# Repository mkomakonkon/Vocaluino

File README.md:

# Vocaluino
MIDI device for playing drum, vocal, PSG, etc with Arduino.

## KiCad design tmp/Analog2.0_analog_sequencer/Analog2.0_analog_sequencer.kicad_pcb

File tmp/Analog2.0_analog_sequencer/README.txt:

本データはAnalog2.0のアナログシーケンサーを改良したものです。
ライセンスはAnalog2.0に従ってください。

Analog2.0のホームページ
https://gaje.jp/analog20/

デモ動画
https://youtu.be/-u9PDCDGB98

CADデータはKiCAD用です。
配置配線案は秋月の下記ユニバーサル基板用の物です。
【P-02188】　両面ガラス・ユニバーサル基板　大タイプ２．５４ｍｍピッチ　（２１０×１５５ｍｍ）
フォンジャックは、お手製の変換基板を使ってて参考にならないと思うので修正してください。

変更内容-----------------------------------------------
オリジナルはシーケンサーが動作していない時も
Gate outが出続けるため、シーケンサー停止時に
Gate outを止めるための変更をした。

・4051の出力をダイオードでORして
Gate out制御用トランジスタのベースに入力することで、
4051が動作しているときのみコレクタを流れるGate out信号をON。
それ以外はGate out信号をOFF。
出力を低インピーダンスにするためエミッタフォロワとする。

・スイッチOFF時も上記回路が動作するように
スイッチの位置を変更。

・念のため回路図に記載のないパスコンを追加。

制約事項-----------------------------------------------
変更を最小限にするため以下の制約あり。
・Gate outは非同期で自走しているため、
　スタートのタイミングによっては1発目の音が出ない。
・Gate out→4051の遅延を吸収していないため
　Gate out OFF直前に不要なパルスが出る。
・Gate out信号は電源よりレベルが低いため
　5V電源を使用する場合は出力にバッファを設けた方が良い。
　12V電源であれば実害はないが、5V入力の機器にはGate outを接続しないこと。
　(Analog2.0は問題ないはず）)

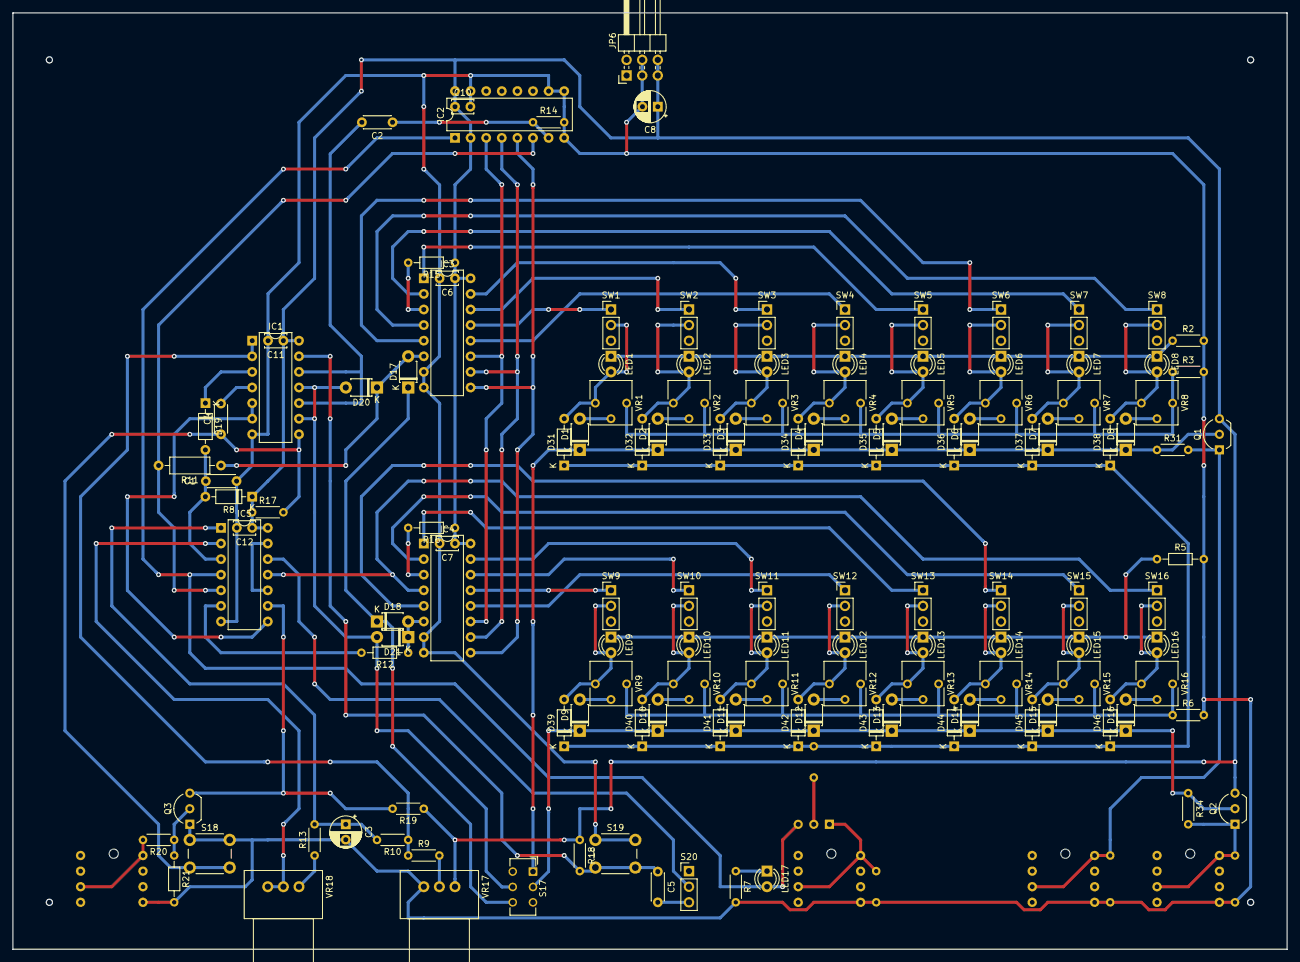
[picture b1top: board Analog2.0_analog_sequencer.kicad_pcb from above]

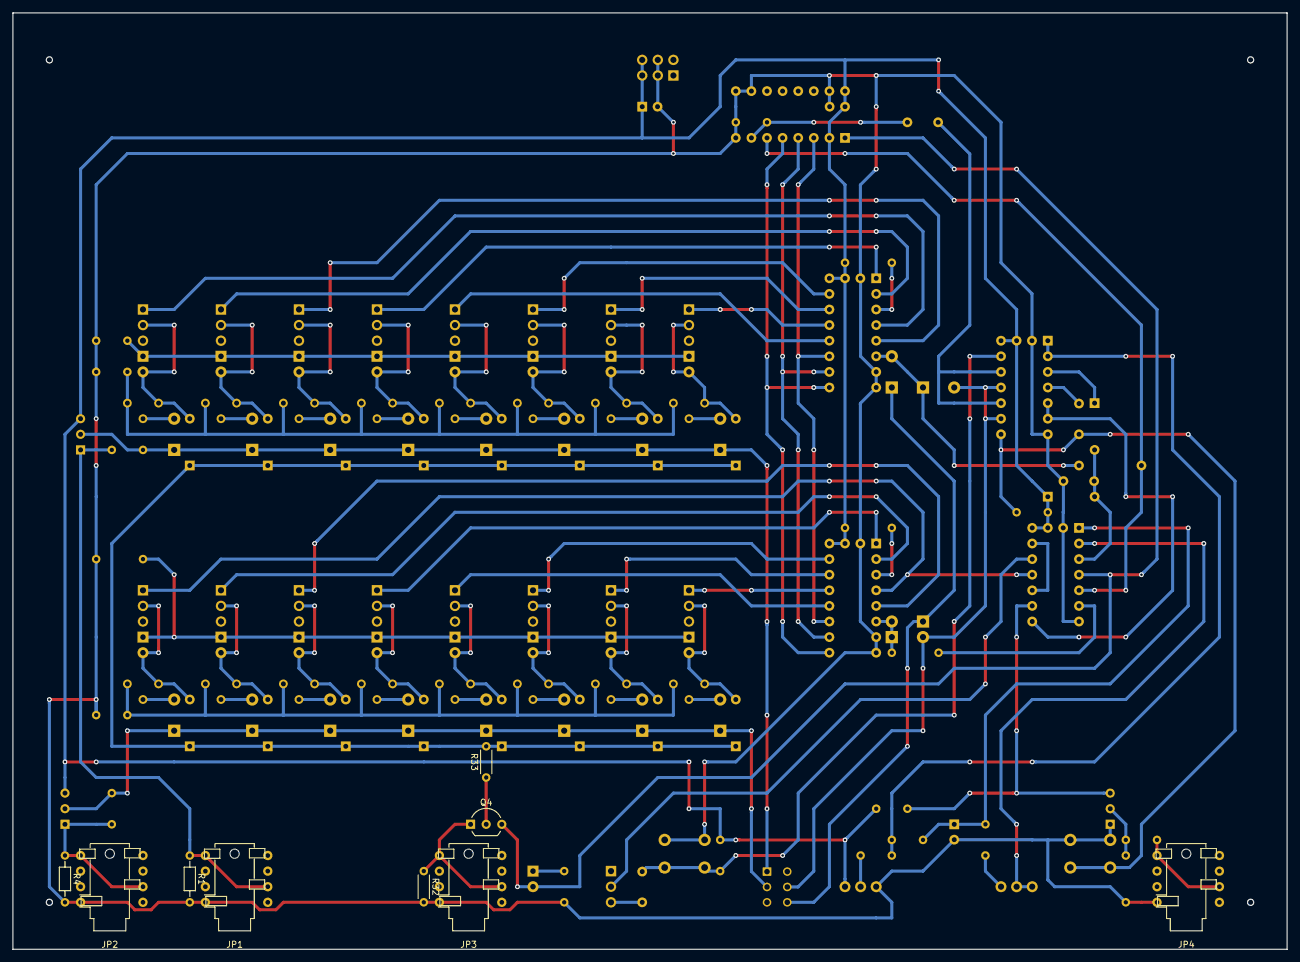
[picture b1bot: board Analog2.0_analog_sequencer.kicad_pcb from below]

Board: 2 copper layers, 207.5 x 152.5 mm, 142 parts (9 on the bottom side), 93 nets.

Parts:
C1: 0.022u; C_Disc_D4.3mm_W1.9mm_P5.00mm
C2, C4, C5: 0.1u; C_Disc_D4.3mm_W1.9mm_P5.00mm
C3: 22u; CP_Radial_D5.0mm_P2.50mm
C6, C7, C10, C11, C12: 0.1u; C_Disc_D3.4mm_W2.1mm_P2.50mm
C8: 100u; CP_Radial_D5.0mm_P2.50mm
D1, D2, D3, D4, D5, D6, D7, D8, D9, D10, D11, D12, D13, D14, D15, D16: D; D_T-1_P5.08mm_Horizontal
D17, D18, D20, D21: 1N4148; D_T-1_P5.08mm_Horizontal
D19: 1N4148; D_DO-35_SOD27_P7.62mm_Horizontal
D31, D32, D33, D34, D35, D36, D37, D38, D39, D40, D41, D42, D43, D44, D45, D46: D; D_DO-35_SOD27_P7.62mm_Horizontal
IC1: 4011; DIP-14_W7.62mm
IC2: 4520; DIP-16_W7.62mm
IC3, IC4: 4051; DIP-16_W7.62mm
IC5: 4584; DIP-14_W7.62mm
JP1: CV_OUT1; Jack_3.5mm_HSJ1828
JP2: CV_OUT2; Jack_3.5mm_HSJ1828
JP3: Gate_Out; Jack_3.5mm_HSJ1828
JP4: Gate_In; Jack_3.5mm_HSJ1828
JP6: Conn_02x03_Counter_Clockwise; PinHeader_2x03_P2.54mm_Horizontal
LED1, LED2, LED3, LED4, LED5, LED6, LED7, LED8, LED9, LED10, LED11, LED12, LED13, LED14, LED15, LED16, LED17: LED; LED_D3.0mm
Q1, Q2, Q3, Q4: 2N3904; TO-92_Inline_Wide
R1, R4: 2.2K; R_Axial_DIN0204_L3.6mm_D1.6mm_P7.62mm_Horizontal
R2: 820; R_Axial_DIN0204_L3.6mm_D1.6mm_P5.08mm_Horizontal
R3, R6: 3.3K; R_Axial_DIN0204_L3.6mm_D1.6mm_P5.08mm_Horizontal
R5: 820; R_Axial_DIN0204_L3.6mm_D1.6mm_P7.62mm_Horizontal
R7: 2.2K; R_Axial_DIN0204_L3.6mm_D1.6mm_P5.08mm_Horizontal
R8: 10K; D_DO-35_SOD27_P7.62mm_Horizontal
R9: 4.7M; R_Axial_DIN0204_L3.6mm_D1.6mm_P5.08mm_Horizontal
R10, R31, R34: 1M; R_Axial_DIN0204_L3.6mm_D1.6mm_P5.08mm_Horizontal
R11: 100K; R_Axial_DIN0207_L6.3mm_D2.5mm_P10.16mm_Horizontal
R12, R21: 100K; R_Axial_DIN0204_L3.6mm_D1.6mm_P7.62mm_Horizontal
R13, R14: 4.7K; R_Axial_DIN0204_L3.6mm_D1.6mm_P5.08mm_Horizontal
R15, R16: 220; R_Axial_DIN0204_L3.6mm_D1.6mm_P7.62mm_Horizontal
R17, R18: 10K; R_Axial_DIN0204_L3.6mm_D1.6mm_P5.08mm_Horizontal
R19: 22K; R_Axial_DIN0204_L3.6mm_D1.6mm_P5.08mm_Horizontal
R20, R32, R33: 47K; R_Axial_DIN0204_L3.6mm_D1.6mm_P5.08mm_Horizontal
S17: Para/Seri; SW_CuK_JS202011CQN_DPDT_Straight
S18: SW_Start; SW_PUSH_6mm_H5mm
S19: SW_Stop; SW_PUSH_6mm_H5mm
S20: SW_Push_SPDT; PinHeader_1x03_P2.54mm_Vertical
SW1, SW2, SW3, SW4, SW5, SW6, SW7, SW8, SW9, SW10, SW11, SW12, SW13, SW14, SW15, SW16: SW_SPDT; PinHeader_1x03_P2.54mm_Vertical
VR1, VR2, VR3, VR4, VR5, VR6, VR7, VR8, VR9, VR10, VR11, VR12, VR13, VR14, VR15, VR16: B50K; Potentiometer_Vishay_T73YP_Vertical
VR17, VR18: B50K; Potentiometer_Vishay_248GJ-249GJ_Single_Horizontal

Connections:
+12V: C6.1, C7.1, C8.1, C10.1, C11.1, C12.1, IC1.14, IC2.2, IC2.16, IC3.16, IC4.16, IC5.14, JP6.5, JP6.6, Q1.3, Q2.3, R8.1, R15.1, R16.1, R17.1, R18.1, R19.1, VR17.3
CV_OUT1: JP1.R, JP1.T, Q1.1, R1.1, R31.2
CV_OUT2: JP2.R, JP2.T, Q2.1, R4.1, R34.2
GND: C1.2, C3.2, C6.2, C7.2, C8.2, C10.2, C11.2, C12.2, IC1.7, IC2.8, IC2.9, IC2.10, IC2.15, IC3.7, IC3.8, IC4.7, IC4.8, IC5.7, JP1.S, JP2.S, JP3.S, JP4.S, JP6.3, JP6.4, Q3.1, R1.2, R2.2, R3.2, R4.2, R5.2, R6.2, R7.2, R14.2, R21.2, R32.2, S18.1, S19.1, VR17.1
Gate_In: JP4.R, JP4.T, R20.2
Gate_Out: JP3.R, JP3.T, Q4.1, R32.1
unnamed: C1.1, D19.2, IC5.3, R8.2
unnamed: C2.1, IC2.7, R14.1
unnamed: C2.2, IC1.10, IC1.12
unnamed: C3.1, IC5.1, R10.2, R13.2
unnamed: C4.1, IC1.8, R17.2, S18.2
unnamed: C4.2, IC1.4
unnamed: C5.1, IC1.13, R18.2, S19.2
unnamed: C5.2, S20.3
unnamed: D1.1, D2.1, D3.1, D4.1, D5.1, D6.1, D7.1, D8.1, Q1.2, R31.1, S17.1
unnamed: D1.2, VR1.2
unnamed: D2.2, VR2.2
unnamed: D3.2, VR3.2
unnamed: D4.2, VR4.2
unnamed: D5.2, VR5.2
unnamed: D6.2, VR6.2
unnamed: D7.2, VR7.2
unnamed: D8.2, VR8.2
unnamed: D9.2, VR9.2
unnamed: D9.1, D10.1, D11.1, D12.1, D13.1, D14.1, D15.1, D16.1, Q2.2, R34.1, S17.2
unnamed: D10.2, VR10.2
unnamed: D11.2, VR11.2
unnamed: D12.2, VR12.2
unnamed: D13.2, VR13.2
unnamed: D14.2, VR14.2
unnamed: D15.2, VR15.2
unnamed: D16.2, VR16.2
unnamed: D17.1, D18.1, S17.6
unnamed: D17.2, D20.1, IC3.6, R11.1
unnamed: D18.2, D21.1, IC4.6, R12.1
unnamed: D19.1, IC1.3
unnamed: D20.2, D21.2, IC1.9, IC1.11, S17.5
unnamed: D31.1, D32.1, D33.1, D34.1, D35.1, D36.1, D37.1, D38.1, D39.1, D40.1, D41.1, D42.1, D43.1, D44.1, D45.1, D46.1, R33.2
unnamed: D31.2, LED1.2, SW1.2, VR1.1
unnamed: D32.2, LED2.2, SW2.2, VR2.1
unnamed: D33.2, LED3.2, SW3.2, VR3.1
unnamed: D34.2, LED4.2, SW4.2, VR4.1
unnamed: D35.2, LED5.2, SW5.2, VR5.1
unnamed: D36.2, LED6.2, SW6.2, VR6.1
unnamed: D37.2, LED7.2, SW7.2, VR7.1
unnamed: D38.2, LED8.2, SW8.2, VR8.1
unnamed: D39.2, LED9.2, SW9.2, VR9.1
unnamed: D40.2, LED10.2, SW10.2, VR10.1
unnamed: D41.2, LED11.2, SW11.2, VR11.1
unnamed: D42.2, LED12.2, SW12.2, VR12.1
unnamed: D43.2, LED13.2, SW13.2, VR13.1
unnamed: D44.2, LED14.2, SW14.2, VR14.1
unnamed: D45.2, LED15.2, SW15.2, VR15.1
unnamed: D46.2, LED16.2, SW16.2, VR16.1
unnamed: IC1.1, IC1.2, R9.1, R10.1
unnamed: IC1.5, IC1.6, IC5.8
unnamed: IC2.1, IC5.4, LED17.2, Q4.3
unnamed: IC2.3, IC3.11, IC4.11
unnamed: IC2.4, IC3.10, IC4.10
unnamed: IC2.5, IC3.9, IC4.9
unnamed: IC2.6, IC5.5, R11.2
unnamed: IC3.1, SW5.1
unnamed: IC3.2, SW7.1
unnamed: IC3.3, R15.2
unnamed: IC3.4, SW8.1
unnamed: IC3.5, SW6.1
unnamed: IC3.12, SW4.1
unnamed: IC3.13, SW1.1
unnamed: IC3.14, SW2.1
unnamed: IC3.15, SW3.1
unnamed: IC4.1, SW13.1
unnamed: IC4.2, SW15.1
unnamed: IC4.3, R16.2
unnamed: IC4.4, IC5.11, SW16.1
unnamed: IC4.5, SW14.1
unnamed: IC4.12, SW12.1
unnamed: IC4.13, SW9.1
unnamed: IC4.14, SW10.1
unnamed: IC4.15, SW11.1
unnamed: IC5.2, VR18.1, VR18.2
unnamed: IC5.6, R12.2
unnamed: IC5.9, Q3.3, R19.2
unnamed: IC5.10, IC5.13
unnamed: IC5.12, S20.2
unnamed: LED1.1, LED2.1, LED3.1, LED4.1, LED5.1, LED6.1, LED7.1, LED8.1, R2.1
unnamed: LED9.1, LED10.1, LED11.1, LED12.1, LED13.1, LED14.1, LED15.1, LED16.1, R5.1
unnamed: LED17.1, R7.1
unnamed: Q3.2, R20.1, R21.1
unnamed: Q4.2, R33.1
unnamed: R3.1, VR1.3, VR2.3, VR3.3, VR4.3, VR5.3, VR6.3, VR7.3, VR8.3
unnamed: R6.1, VR9.3, VR10.3, VR11.3, VR12.3, VR13.3, VR14.3, VR15.3, VR16.3
unnamed: R9.2, VR17.2
unnamed: R13.1, VR18.3

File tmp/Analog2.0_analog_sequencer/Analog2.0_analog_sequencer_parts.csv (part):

Reference, Value, Footprint, Datasheet
"R15","220","Resistor_THT:R_Axial_DIN0204_L3.6mm_D1.6mm_P5.08mm_Horizontal","~"
"IC3","4051","Package_DIP:DIP-16_W7.62mm","http://www.intersil.com/content/dam/Intersil/documents/cd40/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"
"D1","D","Diode_THT:D_T-1_P5.08mm_Horizontal","~"
"SW1","SW_Push_SPDT","Connector_PinHeader_2.54mm:PinHeader_1x03_P2.54mm_Vertical",""
"Q1","2N3904","Package_TO_SOT_THT:TO-92_Inline_Wide","https://www.fairchildsemi.com/datasheets/2N/2N3904.pdf"
"R31","100K","Resistor_THT:R_Axial_DIN0204_L3.6mm_D1.6mm_P5.08mm_Horizontal","~"
"R1","2.2K","Resistor_THT:R_Axial_DIN0204_L3.6mm_D1.6mm_P5.08mm_Horizontal","~"
"LED1","LED","LED_THT:LED_D3.0mm","~"
"LED2","LED","LED_THT:LED_D3.0mm","~"
"LED3","LED","LED_THT:LED_D3.0mm","~"
"LED4","LED","LED_THT:LED_D3.0mm","~"
"LED5","LED","LED_THT:LED_D3.0mm","~"
"LED6","LED","LED_THT:LED_D3.0mm","~"
"LED7","LED","LED_THT:LED_D3.0mm","~"
"LED8","LED","LED_THT:LED_D3.0mm","~"
"D2","D","Diode_THT:D_T-1_P5.08mm_Horizontal","~"
"D3","D","Diode_THT:D_T-1_P5.08mm_Horizontal","~"
"D4","D","Diode_THT:D_T-1_P5.08mm_Horizontal","~"
"D5","D","Diode_THT:D_T-1_P5.08mm_Horizontal","~"
"D6","D","Diode_THT:D_T-1_P5.08mm_Horizontal","~"
"D7","D","Diode_THT:D_T-1_P5.08mm_Horizontal","~"
"D8","D","Diode_THT:D_T-1_P5.08mm_Horizontal","~"
"SW2","SW_Push_SPDT","Connector_PinHeader_2.54mm:PinHeader_1x03_P2.54mm_Vertical",""
"SW3","SW_Push_SPDT","Connector_PinHeader_2.54mm:PinHeader_1x03_P2.54mm_Vertical",""
"SW4","SW_Push_SPDT","Connector_PinHeader_2.54mm:PinHeader_1x03_P2.54mm_Vertical",""
"SW5","SW_Push_SPDT","Connector_PinHeader_2.54mm:PinHeader_1x03_P2.54mm_Vertical",""
"SW6","SW_Push_SPDT","Connector_PinHeader_2.54mm:PinHeader_1x03_P2.54mm_Vertical",""
"SW7","SW_Push_SPDT","Connector_PinHeader_2.54mm:PinHeader_1x03_P2.54mm_Vertical",""
"SW8","SW_Push_SPDT","Connector_PinHeader_2.54mm:PinHeader_1x03_P2.54mm_Vertical",""
"VR1","B50K","Potentiometer_THT:Potentiometer_Vishay_T73YP_Vertical","~"
"R2","820","Resistor_THT:R_Axial_DIN0204_L3.6mm_D1.6mm_P5.08mm_Horizontal","~"
"R16","220","Resistor_THT:R_Axial_DIN0204_L3.6mm_D1.6mm_P5.08mm_Horizontal","~"
"IC4","4051","Package_DIP:DIP-16_W7.62mm","http://www.intersil.com/content/dam/Intersil/documents/cd40/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"
"VR2","B50K","Potentiometer_THT:Potentiometer_Vishay_T73YP_Vertical","~"
"VR3","B50K","Potentiometer_THT:Potentiometer_Vishay_T73YP_Vertical","~"
"VR4","B50K","Potentiometer_THT:Potentiometer_Vishay_T73YP_Vertical","~"
"VR5","B50K","Potentiometer_THT:Potentiometer_Vishay_T73YP_Vertical","~"
"VR6","B50K","Potentiometer_THT:Potentiometer_Vishay_T73YP_Vertical","~"
"VR7","B50K","Potentiometer_THT:Potentiometer_Vishay_T73YP_Vertical","~"
"VR8","B50K","Potentiometer_THT:Potentiometer_Vishay_T73YP_Vertical","~"
"R3","3.3K","Resistor_THT:R_Axial_DIN0204_L3.6mm_D1.6mm_P5.08mm_Horizontal","~"
"D9","D","Diode_THT:D_T-1_P5.08mm_Horizontal","~"
"SW9","SW_Push_SPDT","Connector_PinHeader_2.54mm:PinHeader_1x03_P2.54mm_Vertical",""
"Q2","2N3904","Package_TO_SOT_THT:TO-92_Inline_Wide","https://www.fairchildsemi.com/datasheets/2N/2N3904.pdf"
"R34","100K","Resistor_THT:R_Axial_DIN0204_L3.6mm_D1.6mm_P5.08mm_Horizontal","~"
"R4","2.2K","Resistor_THT:R_Axial_DIN0204_L3.6mm_D1.6mm_P5.08mm_Horizontal","~"
"LED9","LED","LED_THT:LED_D3.0mm","~"
"LED10","LED","LED_THT:LED_D3.0mm","~"
"LED11","LED","LED_THT:LED_D3.0mm","~"
"LED12","LED","LED_THT:LED_D3.0mm","~"
"LED13","LED","LED_THT:LED_D3.0mm","~"
"LED14","LED","LED_THT:LED_D3.0mm","~"
"LED15","LED","LED_THT:LED_D3.0mm","~"
"LED16","LED","LED_THT:LED_D3.0mm","~"
"D10","D","Diode_THT:D_T-1_P5.08mm_Horizontal","~"
"D11","D","Diode_THT:D_T-1_P5.08mm_Horizontal","~"
"D12","D","Diode_THT:D_T-1_P5.08mm_Horizontal","~"
"D13","D","Diode_THT:D_T-1_P5.08mm_Horizontal","~"
"D14","D","Diode_THT:D_T-1_P5.08mm_Horizontal","~"
"D15","D","Diode_THT:D_T-1_P5.08mm_Horizontal","~"
"D16","D","Diode_THT:D_T-1_P5.08mm_Horizontal","~"
"SW10","SW_Push_SPDT","Connector_PinHeader_2.54mm:PinHeader_1x03_P2.54mm_Vertical",""
"SW11","SW_Push_SPDT","Connector_PinHeader_2.54mm:PinHeader_1x03_P2.54mm_Vertical",""
"SW12","SW_Push_SPDT","Connector_PinHeader_2.54mm:PinHeader_1x03_P2.54mm_Vertical",""
"SW13","SW_Push_SPDT","Connector_PinHeader_2.54mm:PinHeader_1x03_P2.54mm_Vertical",""
"SW14","SW_Push_SPDT","Connector_PinHeader_2.54mm:PinHeader_1x03_P2.54mm_Vertical",""
"SW15","SW_Push_SPDT","Connector_PinHeader_2.54mm:PinHeader_1x03_P2.54mm_Vertical",""
"SW16","SW_Push_SPDT","Connector_PinHeader_2.54mm:PinHeader_1x03_P2.54mm_Vertical",""
"VR9","B50K","Potentiometer_THT:Potentiometer_Vishay_T73YP_Vertical","~"
"R5","820","Resistor_THT:R_Axial_DIN0204_L3.6mm_D1.6mm_P5.08mm_Horizontal","~"
"VR10","B50K","Potentiometer_THT:Potentiometer_Vishay_T73YP_Vertical","~"
"VR11","B50K","Potentiometer_THT:Potentiometer_Vishay_T73YP_Vertical","~"
"VR12","B50K","Potentiometer_THT:Potentiometer_Vishay_T73YP_Vertical","~"
"VR13","B50K","Potentiometer_THT:Potentiometer_Vishay_T73YP_Vertical","~"
"VR14","B50K","Potentiometer_THT:Potentiometer_Vishay_T73YP_Vertical","~"
"VR15","B50K","Potentiometer_THT:Potentiometer_Vishay_T73YP_Vertical","~"
"VR16","B50K","Potentiometer_THT:Potentiometer_Vishay_T73YP_Vertical","~"
"R6","3.3K","Resistor_THT:R_Axial_DIN0204_L3.6mm_D1.6mm_P5.08mm_Horizontal","~"
"S17","Para/Seri","Button_Switch_THT:SW_CuK_JS202011CQN_DPDT_Straight",""
"IC2","4520","Package_DIP:DIP-16_W7.62mm","http://www.intersil.com/content/dam/Intersil/documents/cd45/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"
"D18","1N4148","Diode_THT:D_T-1_P5.08mm_Horizontal","~"
"D17","1N4148","Diode_THT:D_T-1_P5.08mm_Horizontal","~"
"R11","100K","Resistor_THT:R_Axial_DIN0204_L3.6mm_D1.6mm_P5.08mm_Horizontal","~"
"IC5","4584","Package_DIP:DIP-14_W7.62mm",""
"R12","100K","Resistor_THT:R_Axial_DIN0204_L3.6mm_D1.6mm_P5.08mm_Horizontal","~"
"D21","1N4148","Diode_THT:D_T-1_P5.08mm_Horizontal","~"
"D20","1N4148","Diode_THT:D_T-1_P5.08mm_Horizontal","~"
"IC1","4011","Package_DIP:DIP-14_W7.62mm","http://www.intersil.com/content/dam/Intersil/documents/cd40/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"
"C7","0.1u","Capacitor_THT:C_Disc_D3.4mm_W2.1mm_P2.50mm","~"
"C6","0.1u","Capacitor_THT:C_Disc_D3.4mm_W2.1mm_P2.50mm","~"
"C2","0.1u","Capacitor_THT:C_Disc_D4.3mm_W1.9mm_P5.00mm","~"
"R14","4.7K","Resistor_THT:R_Axial_DIN0204_L3.6mm_D1.6mm_P5.08mm_Horizontal","~"
"C1","0.022u","Capacitor_THT:C_Disc_D4.3mm_W1.9mm_P5.00mm","~"
"R8","10K","Resistor_THT:R_Axial_DIN0204_L3.6mm_D1.6mm_P5.08mm_Horizontal","~"
"R7","2.2K","Resistor_THT:R_Axial_DIN0204_L3.6mm_D1.6mm_P5.08mm_Horizontal","~"
"LED17","LED","LED_THT:LED_D3.0mm","~"
"D19","1N4148","Diode_THT:D_T-1_P5.08mm_Horizontal","~"
"VR17","B50K","Potentiometer_THT:Potentiometer_Vishay_248GJ-249GJ_Single_Horizontal","~"
"VR18","B50K","Potentiometer_THT:Potentiometer_Vishay_248GJ-249GJ_Single_Horizontal","~"
"R9","4.7M","Resistor_THT:R_Axial_DIN0204_L3.6mm_D1.6mm_P5.08mm_Horizontal","~"
"R10","1M","Resistor_THT:R_Axial_DIN0204_L3.6mm_D1.6mm_P5.08mm_Horizontal","~"
"R13","4.7K","Resistor_THT:R_Axial_DIN0204_L3.6mm_D1.6mm_P5.08mm_Horizontal","~"
"C3","22u","Capacitor_THT:CP_Radial_D5.0mm_P2.50mm","~"
"R18","10K","Resistor_THT:R_Axial_DIN0204_L3.6mm_D1.6mm_P5.08mm_Horizontal","~"
"S19","SW_Start","Button_Switch_THT:SW_PUSH_6mm_H5mm",""
"C5","0.1u","Capacitor_THT:C_Disc_D4.3mm_W1.9mm_P5.00mm","~"
"S20","SW_Push_SPDT","Connector_PinHeader_2.54mm:PinHeader_1x03_P2.54mm_Vertical",""
"R20","47K","Resistor_THT:R_Axial_DIN0204_L3.6mm_D1.6mm_P5.08mm_Horizontal","~"
"R21","100K","Resistor_THT:R_Axial_DIN0204_L3.6mm_D1.6mm_P5.08mm_Horizontal","~"
"Q3","2N3904","Package_TO_SOT_THT:TO-92_Inline_Wide","https://www.fairchildsemi.com/datasheets/2N/2N3904.pdf"
"R19","22K","Resistor_THT:R_Axial_DIN0204_L3.6mm_D1.6mm_P5.08mm_Horizontal","~"
"C4","0.1u","Capacitor_THT:C_Disc_D4.3mm_W1.9mm_P5.00mm","~"
"R17","10K","Resistor_THT:R_Axial_DIN0204_L3.6mm_D1.6mm_P5.08mm_Horizontal","~"
"S18","SW_Start","Button_Switch_THT:SW_PUSH_6mm_H5mm",""
"JP6","Conn_02x03_Counter_Clockwise","Connector_PinHeader_2.54mm:PinHeader_2x03_P2.54mm_Horizontal","~"
"C8","100u","Capacitor_THT:CP_Radial_D5.0mm_P2.50mm","~"
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
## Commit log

2018-10-16 Add files via upload
    スイッチとボリュームを忘れていたので追記
2019-10-09 Create dmy
2019-10-22 Create test
